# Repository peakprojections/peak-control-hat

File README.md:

# peak-control-hat
KiCad schematic and build files for the Peak Control Hat used with the Peak Controller Raspberry Pi

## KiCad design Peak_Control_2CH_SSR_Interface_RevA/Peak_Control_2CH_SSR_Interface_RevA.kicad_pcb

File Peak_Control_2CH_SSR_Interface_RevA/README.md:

# Peak Control 2CH SSR Interface Rev A1.1

This directory is the first-revision **simple/production-oriented 2-Channel SSR version** of the Peak Projections Power Control Interface Board.

It is intentionally separate from `Peak_Control_HAT_RevA`, which remains the more advanced smart-switch/TPS272C45 design for possible future development. 

It is a scaled down version of the `Peak_Control_SSR_Interface_RevA` which is the 4-channel version.

## Design goals

- Keep the first hardware revision simple, robust, and economical.
- Use Omron PhotoMOS SSRs for isolated 24 V contactor/control outputs.
- Keep mains/load switching off-board; this board controls 24 V contactor coils from low-voltage control circuits only.

## Proposed board

- Raspberry Pi M2.5 mounting pattern
- 24 V control input
- 2 isolated 24 V switched outputs

## Output architecture

Primary SSR: **Omron G3VM-61GR2** (60 V PhotoMOS, SOP-4).

Each output channel is conceptually:

`Pi GPIO -> 390R -> G3VM-61GR2 input LED`

`+24V field -> G3VM-61GR2 output -> SW +24V terminal -> external contactor coil -> field 0V`

Each channel also includes board-side flyback suppression across the output terminals.

## Practical Implementations

This board is designed to work with a Raspberry Pi and has a mounting-hole pattern to be stacked above or below a Pi (long standoffs should be used to keep a distance). 

This board should support any 3.3v output microcontroller connection, it does not have to be a Raspberry Pi.

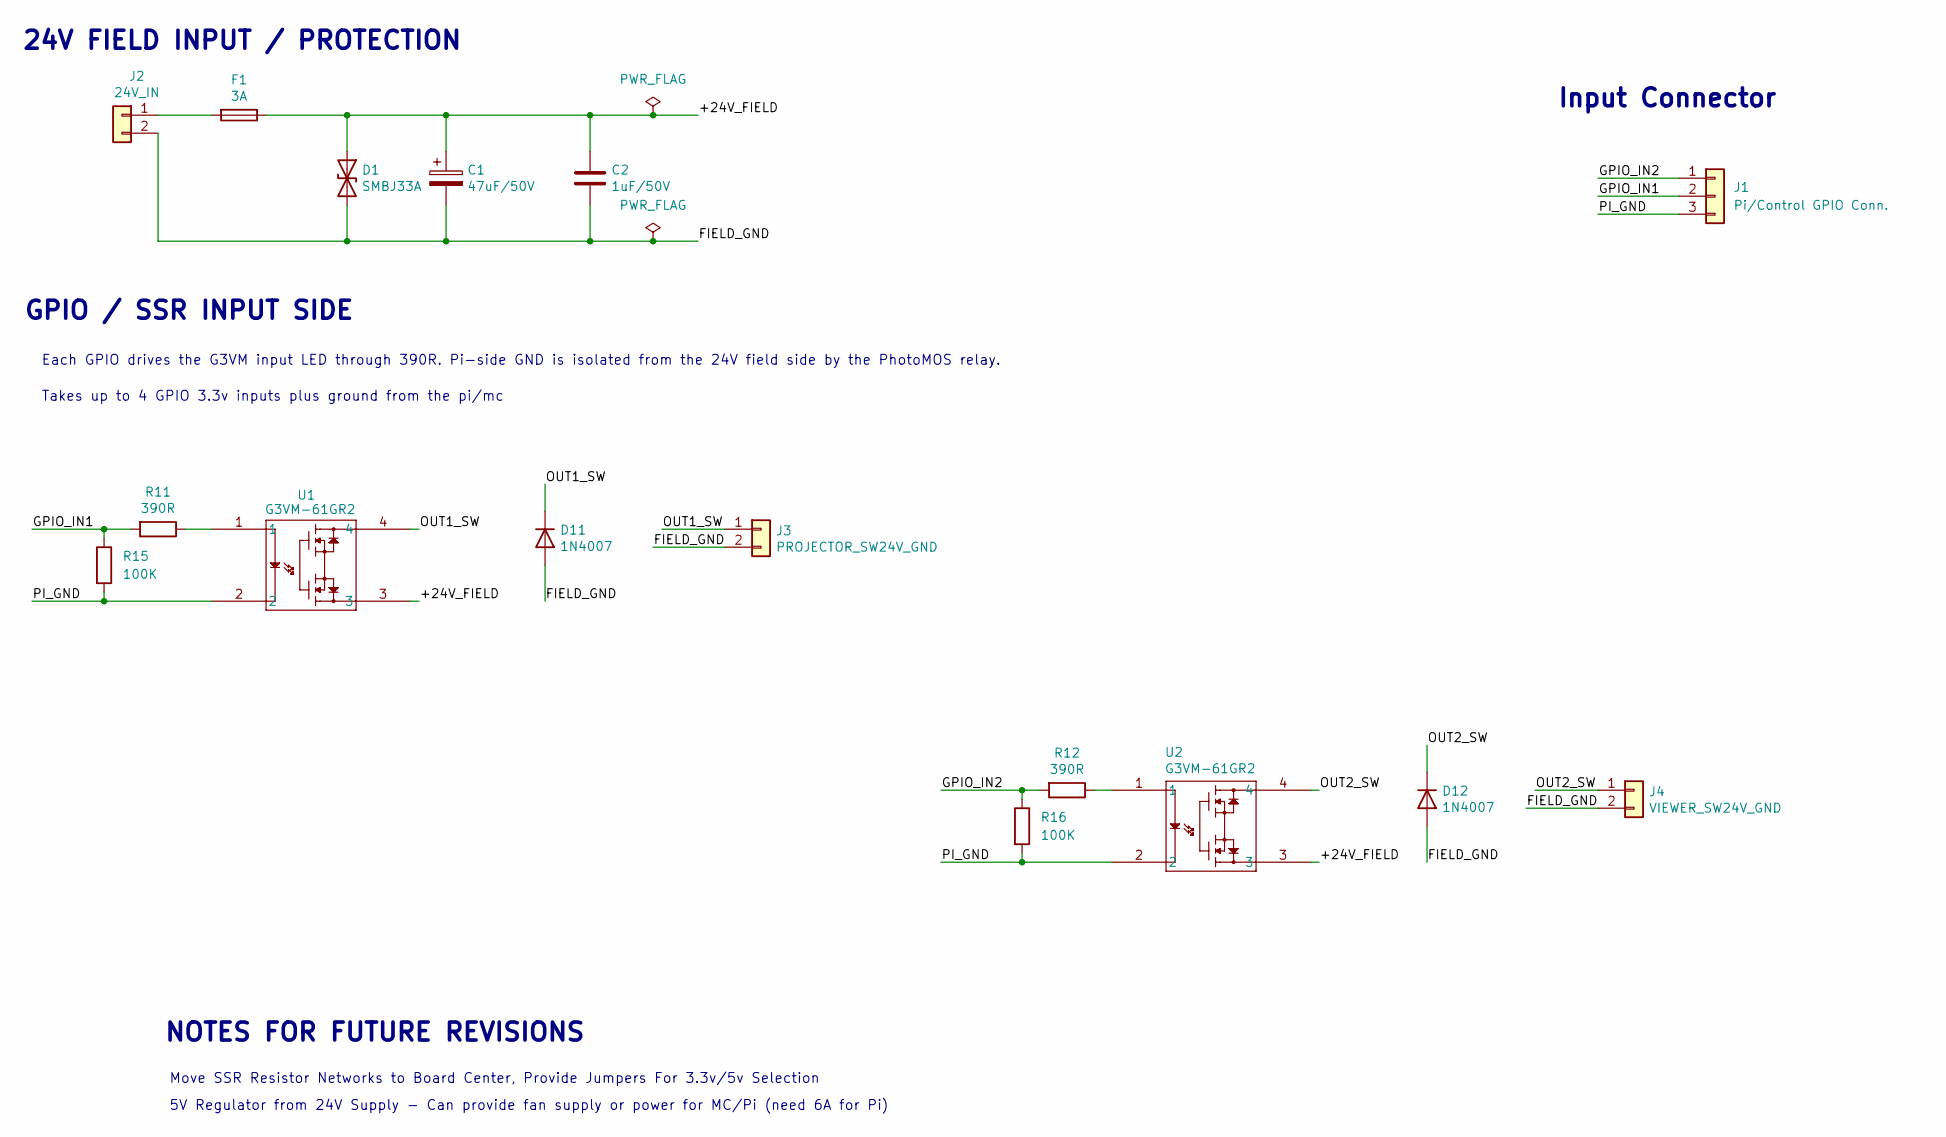
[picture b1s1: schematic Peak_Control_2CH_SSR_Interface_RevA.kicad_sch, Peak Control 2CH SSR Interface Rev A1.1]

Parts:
C1: 47uF/50V; CP_Radial_D8.0mm_P3.50mm; MPN 50RX3047MT78X11.5
C2: 1uF/50V; C_0805_2012Metric_Pad1.18x1.45mm_HandSolder; MPN 08055C105K4T2A
D1: SMBJ33A; D_SMB_Handsoldering; MPN SMBJ33A
D11, D12: 1N4007; D_DO-41_SOD81_P10.16mm_Horizontal; MPN 1N4007
F1: 3A; FUSE-TH_L22.6-W9.0; MPN 5x20 BLX-A XC-7
J1: Pi/Control GPIO Conn.; CONN-TH_3P-P5.08_DIBO_DB128V-5.08-3P-X; MPN DB128V-5.08-3P-GN-S
J2: 24V_IN; CONN-TH_YC0220500000G; MPN YC0220500000G
J3: PROJECTOR_SW24V_GND; CONN-TH_YC0220500000G; MPN YC0220500000G
J4: VIEWER_SW24V_GND; CONN-TH_YC0220500000G; MPN YC0220500000G
R11, R12: 390R; R_0805_2012Metric_Pad1.20x1.40mm_HandSolder; MPN RC0805FR-07390RL
R15, R16: 100K; R_0805_2012Metric_Pad1.20x1.40mm_HandSolder; MPN RC0805FR-07100KL
U1, U2: G3VM-61GR2; G-SOP4_OMR; MPN G3VM-61GR2(TR05)

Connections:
/+24V_FIELD: C1.1, C2.1, D1.1 (A1), F1.1, U1.3, U2.3
/FIELD_GND: C1.2, C2.2, D1.2 (A2), D11.2 (A), D12.2 (A), J2.2, J3.2, J4.2
/GPIO_IN1: J1.2, R11.2, R15.1
/GPIO_IN2: J1.1, R12.2, R16.1
/OUT1_SW: D11.1 (K), J3.1, U1.4
/OUT2_SW: D12.1 (K), J4.1, U2.4
/PI_GND: J1.3, R15.2, R16.2, U1.2, U2.2
unnamed: F1.2, J2.1
unnamed: R11.1, U1.1
unnamed: R12.1, U2.1

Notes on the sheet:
NOTES FOR FUTURE REVISIONS
Each GPIO drives the G3VM input LED through 390R. Pi-side GND is isolated from the 24V field side by the PhotoMOS relay.
5V Regulator from 24V Supply - Can provide fan supply or power for MC/Pi (need 6A for Pi)
Input Connector
24V FIELD INPUT / PROTECTION
GPIO / SSR INPUT SIDE
Move SSR Resistor Networks to Board Center, Provide Jumpers For 3.3v/5v Selection
Takes up to 4 GPIO 3.3v inputs plus ground from the pi/mc

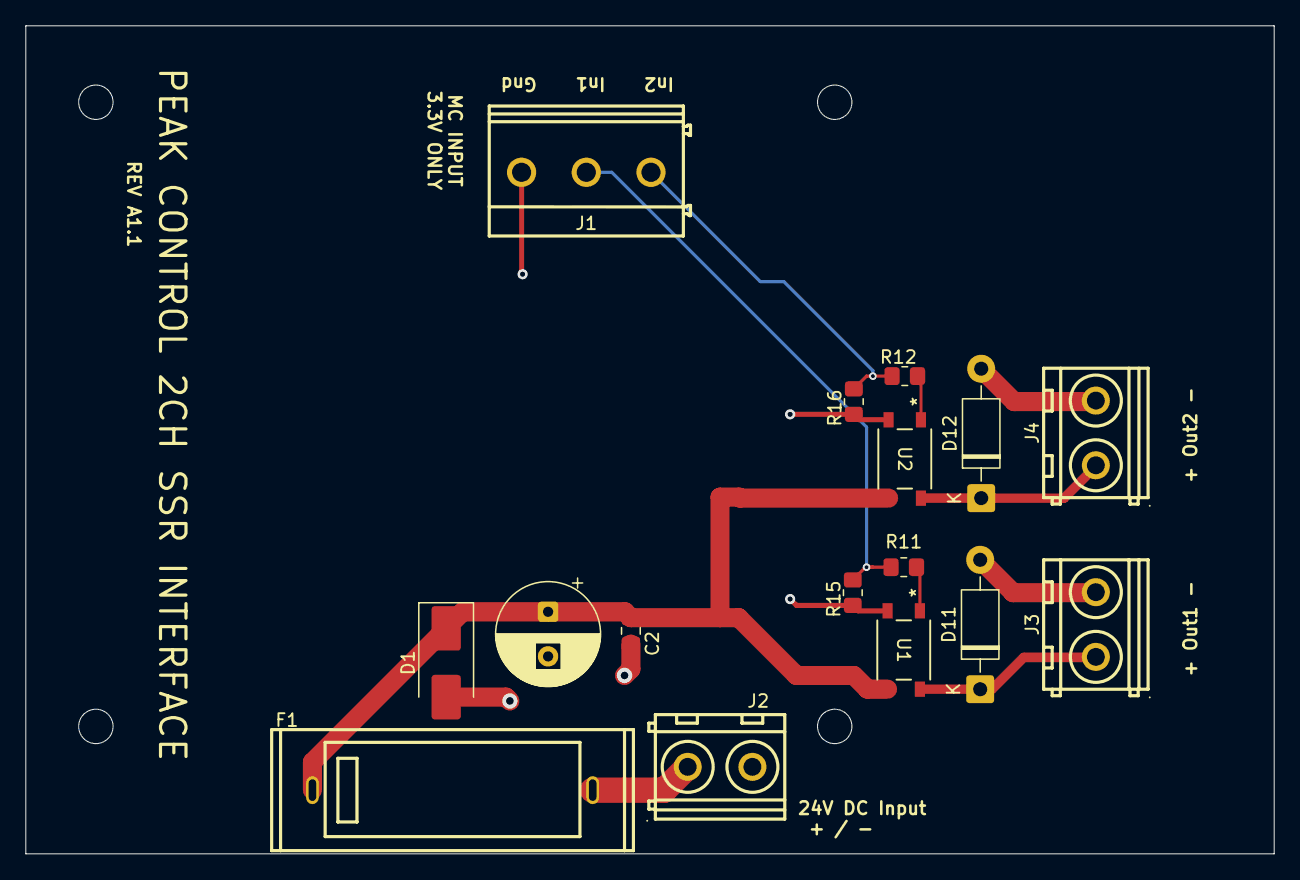
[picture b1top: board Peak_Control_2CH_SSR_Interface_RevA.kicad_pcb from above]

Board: 4 copper layers, 98.0 x 65.0 mm, 16 parts (0 on the bottom side), 10 nets.

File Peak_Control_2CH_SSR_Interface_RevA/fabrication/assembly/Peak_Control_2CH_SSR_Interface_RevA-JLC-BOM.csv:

Comment,Designator,Footprint,LCSC Part #
47uF/50V,C1,CP_Radial_D8.0mm_P3.50mm,C473223
1uF/50V,C2,C_0805_2012Metric_Pad1.18x1.45mm_HandSolder,C779994
SMBJ33A,D1,D_SMB_Handsoldering,C5261717
1N4007,"D11,D12",D_DO-41_SOD81_P10.16mm_Horizontal,C106903
3A,F1,FUSE-TH_L22.6-W9.0,C3131
Pi/Control GPIO Conn.,J1,CONN-TH_3P-P5.08_DIBO_DB128V-5.08-3P-X,C2915640
24V_IN,J2,CONN-TH_YC0220500000G,C2683165
PROJECTOR_SW24V_GND,J3,CONN-TH_YC0220500000G,C2683165
VIEWER_SW24V_GND,J4,CONN-TH_YC0220500000G,C2683165
390R,"R11,R12",R_0805_2012Metric_Pad1.20x1.40mm_HandSolder,C114543
100K,"R15,R16",R_0805_2012Metric_Pad1.20x1.40mm_HandSolder,C96346
G3VM-61GR2,"U1,U2",G-SOP4_OMR,C2653911

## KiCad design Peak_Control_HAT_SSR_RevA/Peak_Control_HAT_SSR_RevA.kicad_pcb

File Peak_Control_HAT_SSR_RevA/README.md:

# Peak Control HAT SSR Rev A

This directory is the first-revision **simple/production-oriented SSR version** of the Peak Projections Power Control HAT.

It is intentionally separate from `Peak_Control_HAT_RevA`, which remains the more advanced smart-switch/TPS272C45 design for possible future development.

## Design goals

- Keep the first hardware revision simple, robust, and economical.
- Use Omron PhotoMOS SSRs for isolated 24 V contactor/control outputs.
- Preserve the Raspberry Pi GPIO mapping used by the advanced design where practical so software can remain hardware-agnostic.
- Retain the corrected Raspberry Pi HAT mechanical geometry from the existing design.
- Provide I2C expansion directly from the Pi for future diagnostics/display/daughterboards.
- Keep mains/load switching off-board; this HAT controls 24 V contactor coils and low-voltage control circuits only.

## Proposed board

- 115 mm × 70 mm extended HAT-style PCB target
- Raspberry Pi 2×20 stacking header
- Raspberry Pi M2.5 mounting pattern
- 40 mm fan mechanical provision retained
- 24 V control input
- 4 isolated 24 V switched outputs
- 2 field/proof inputs
- 2 IR output connections
- 4-position I2C expansion terminal: `3V3`, `GND`, `SDA`, `SCL`
- 3-wire fan connector: `5V`, `GND`, `TACH`

## Output architecture

Primary SSR: **Omron G3VM-61GR2** (60 V PhotoMOS, SOP-4).

Each output channel is conceptually:

`Pi GPIO -> 390R -> G3VM-61GR2 input LED`

`+24V field -> G3VM-61GR2 output -> SW +24V terminal -> external contactor coil -> field 0V`

Each channel also includes board-side flyback suppression across the output terminals.

## I2C expansion

A dedicated 4-position terminal block is included:

1. 3V3
2. GND
3. SDA (GPIO2 / physical pin 3)
4. SCL (GPIO3 / physical pin 5)

Optional SDA/SCL pull-up footprints are intended to be DNP by default because the Raspberry Pi already supplies I2C pull-ups. Series-resistor footprints allow 0-ohm links initially or modest damping if useful during testing.

Raw I2C should be treated as a short-range internal expansion interface. Longer remote runs should eventually use an appropriate extender, CAN, RS-485, or similar robust field bus.

## Current files

- `Peak_Control_HAT_SSR_RevA.sch` — initial schematic source in KiCad legacy format, ready to open/import and save into the current `.kicad_sch` format.
- `Peak_Control_HAT_SSR_RevA.kicad_pcb` — separate SSR mechanical/placement skeleton using the corrected Pi/header/mounting geometry.
- `Peak_Control_HAT_SSR_RevA.kicad_pro` — project container; KiCad will populate normal project settings when opened/saved.
- `Electrical_Design_SSR_RevA.md` — electrical architecture, protection intent, routing targets, and fabrication hold points.
- `Pin_Map_SSR_RevA.csv` — GPIO/function map for the simplified board.

## Important fabrication note

The G3VM symbols and PCB locations are currently **design placeholders**. The exact Omron G3VM-61GR2 pin numbering and recommended SOP-4 land pattern must be verified and substituted before routing or fabrication. The proof-input, IR-buffer, and fan-control circuits also remain to be finalized.

## Status

The SSR revision is now established as an independent project without modifying the TPS-based design. The next step is to open/import the schematic in KiCad, save it in the current `.kicad_sch` format, then continue detailed schematic capture and verified footprint assignment before routing.

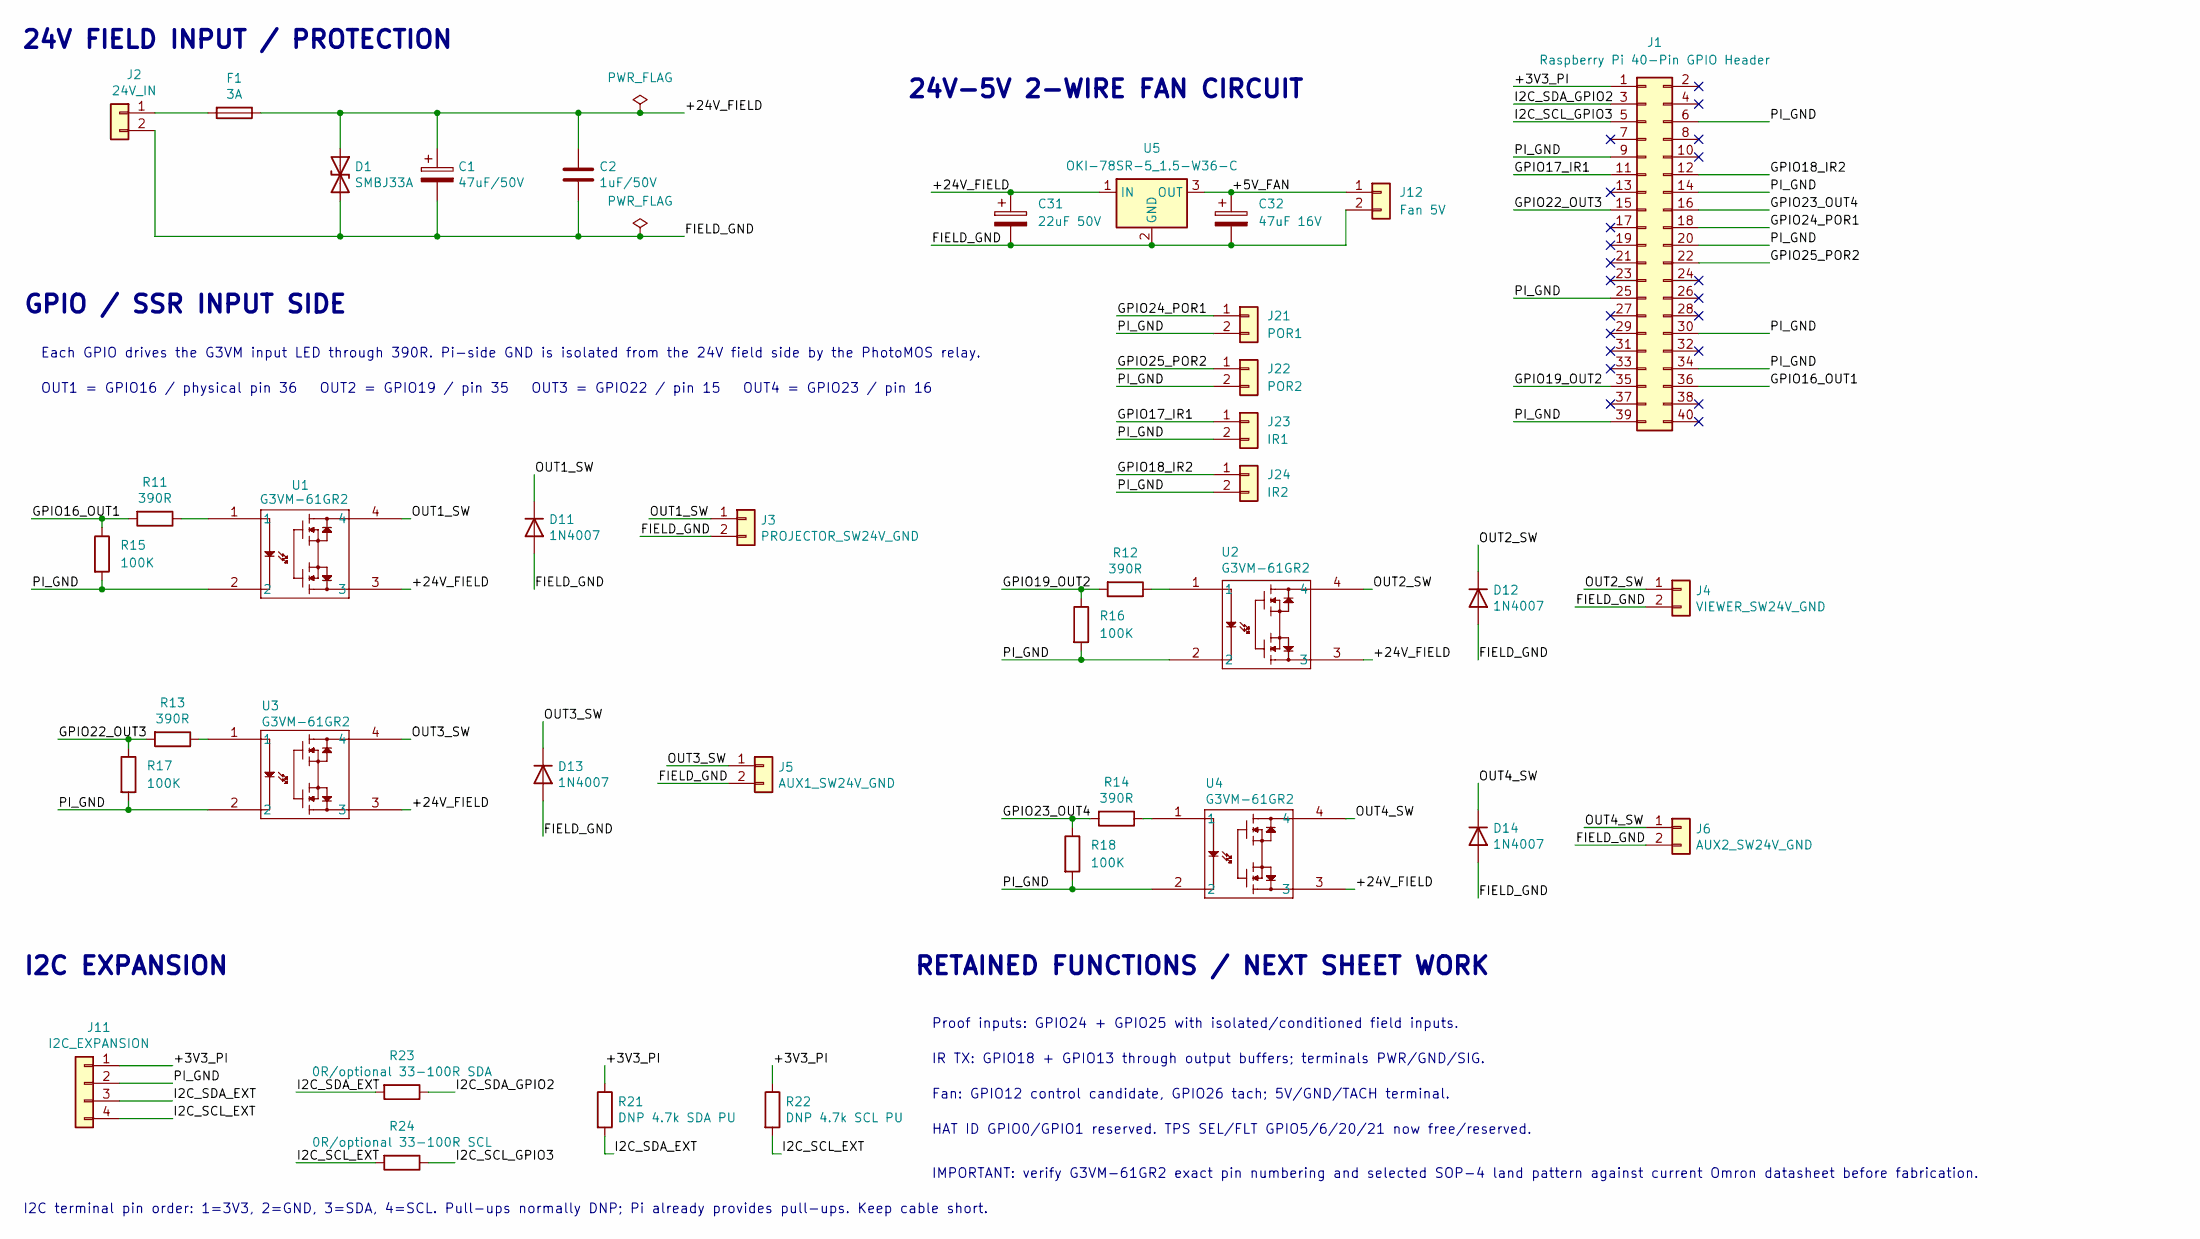
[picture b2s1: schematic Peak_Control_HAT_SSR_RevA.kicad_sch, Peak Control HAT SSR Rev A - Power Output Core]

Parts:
C1: 47uF/50V; CP_Radial_D8.0mm_P3.50mm
C2: 1uF/50V; C_0805_2012Metric_Pad1.18x1.45mm_HandSolder
C31: 22uF 50V; CP_Radial_D5.0mm_P2.00mm
C32: 47uF 16V; CP_Radial_D5.0mm_P2.00mm
D1: SMBJ33A; D_SMB_Handsoldering
D11, D12, D13, D14: 1N4007; D_DO-41_SOD81_P10.16mm_Horizontal
F1: 3A; Fuseholder_Clip-5x20mm_Bel_FC-203-22_Lateral_P17.80x5.00mm_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
J1: Raspberry Pi 40-Pin GPIO Header; PinSocket_2x20_P2.54mm_Vertical
J2: 24V_IN; TerminalBlock_Phoenix_MKDS-1,5-2-5.08_1x02_P5.08mm_Horizont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
J3: PROJECTOR_SW24V_GND; TerminalBlock_Phoenix_MKDS-1,5-2-5.08_1x02_P5.08mm_Horizont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
J4: VIEWER_SW24V_GND; TerminalBlock_Phoenix_MKDS-1,5-2-5.08_1x02_P5.08mm_Horizont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
J5: AUX1_SW24V_GND; TerminalBlock_Phoenix_MKDS-1,5-2-5.08_1x02_P5.08mm_Horizont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
J6: AUX2_SW24V_GND; TerminalBlock_Phoenix_MKDS-1,5-2-5.08_1x02_P5.08mm_Horizont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
J11: I2C_EXPANSION; TerminalBlock_Phoenix_MKDS-1,5-4-5.08_1x04_P5.08mm_Horizont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
J12: Fan 5V; JST_XH_B2B-XH-A_1x02_P2.50mm_Vertical
J21: POR1; TerminalBlock_Phoenix_MKDS-1,5-2-5.08_1x02_P5.08mm_Horizont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
J22: POR2; TerminalBlock_Phoenix_MKDS-1,5-2-5.08_1x02_P5.08mm_Horizont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
J23: IR1; TerminalBlock_Phoenix_MKDS-1,5-2-5.08_1x02_P5.08mm_Horizont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
J24: IR2; TerminalBlock_Phoenix_MKDS-1,5-2-5.08_1x02_P5.08mm_Horizont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
R11, R12, R13, R14: 390R; R_0805_2012Metric_Pad1.20x1.40mm_HandSolder
R15, R16, R17, R18: 100K; R_0805_2012Metric_Pad1.20x1.40mm_HandSolder
R21: DNP 4.7k SDA PU; R_0805_2012Metric_Pad1.20x1.40mm_HandSolder
R22: DNP 4.7k SCL PU; R_0805_2012Metric_Pad1.20x1.40mm_HandSolder
R23: 0R/optional 33-100R SDA; R_0805_2012Metric_Pad1.20x1.40mm_HandSolder
R24: 0R/optional 33-100R SCL; R_0805_2012Metric_Pad1.20x1.40mm_HandSolder
U1, U2, U3, U4: G3VM-61GR2; G-SOP4_OMR
U5: OKI-78SR-5_1.5-W36-C; Converter_DCDC_Murata_OKI-78SR_Vertical

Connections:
/+3V3_PI: J1.1, J11.1, R21.1, R22.1
/+5V_FAN: C32.1, J12.1, U5.3 (OUT)
/+24V_FIELD: C1.1, C2.1, C31.1, D1.1 (A1), F1.1, U1.3, U2.3, U3.3, U4.3, U5.1 (IN)
/FIELD_GND: C1.2, C2.2, C31.2, C32.2, D1.2 (A2), D11.2 (A), D12.2 (A), D13.2 (A), D14.2 (A), J2.2, J3.2, J4.2, J5.2, J6.2, J12.2, U5.2 (GND)
/GPIO16_OUT1: J1.36, R11.2, R15.1
/GPIO17_IR1: J1.11, J23.1
/GPIO18_IR2: J1.12, J24.1
/GPIO19_OUT2: J1.35, R12.2, R16.1
/GPIO22_OUT3: J1.15, R13.2, R17.1
/GPIO23_OUT4: J1.16, R14.2, R18.1
/GPIO24_POR1: J1.18, J21.1
/GPIO25_POR2: J1.22, J22.1
/I2C_SCL_EXT: J11.4, R22.2, R24.2
/I2C_SCL_GPIO3: J1.5, R24.1
/I2C_SDA_EXT: J11.3, R21.2, R23.2
/I2C_SDA_GPIO2: J1.3, R23.1
/OUT1_SW: D11.1 (K), J3.1, U1.4
/OUT2_SW: D12.1 (K), J4.1, U2.4
/OUT3_SW: D13.1 (K), J5.1, U3.4
/OUT4_SW: D14.1 (K), J6.1, U4.4
/PI_GND: J1.6, J1.9, J1.14, J1.20, J1.25, J1.30, J1.34, J1.39, J11.2, J21.2, J22.2, J23.2, J24.2, R15.2, R16.2, R17.2, R18.2, U1.2, U2.2, U3.2, U4.2
unnamed: F1.2, J2.1
unnamed: R11.1, U1.1
unnamed: R12.1, U2.1
unnamed: R13.1, U3.1
unnamed: R14.1, U4.1

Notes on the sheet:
I2C EXPANSION
HAT ID GPIO0/GPIO1 reserved. TPS SEL/FLT GPIO5/6/20/21 now free/reserved.
RETAINED FUNCTIONS / NEXT SHEET WORK
Each GPIO drives the G3VM input LED through 390R. Pi-side GND is isolated from the 24V field side by the PhotoMOS relay.
24V-5V 2-WIRE FAN CIRCUIT
IMPORTANT: verify G3VM-61GR2 exact pin numbering and selected SOP-4 land pattern against current Omron datasheet before fabrication.
24V FIELD INPUT / PROTECTION
GPIO / SSR INPUT SIDE
I2C terminal pin order: 1=3V3, 2=GND, 3=SDA, 4=SCL. Pull-ups normally DNP; Pi already provides pull-ups. Keep cable short.
Proof inputs: GPIO24 + GPIO25 with isolated/conditioned field inputs.
Fan: GPIO12 control candidate, GPIO26 tach; 5V/GND/TACH terminal.
IR TX: GPIO18 + GPIO13 through output buffers; terminals PWR/GND/SIG.
OUT1 = GPIO16 / physical pin 36 OUT2 = GPIO19 / pin 35 OUT3 = GPIO22 / pin 15 OUT4 = GPIO23 / pin 16

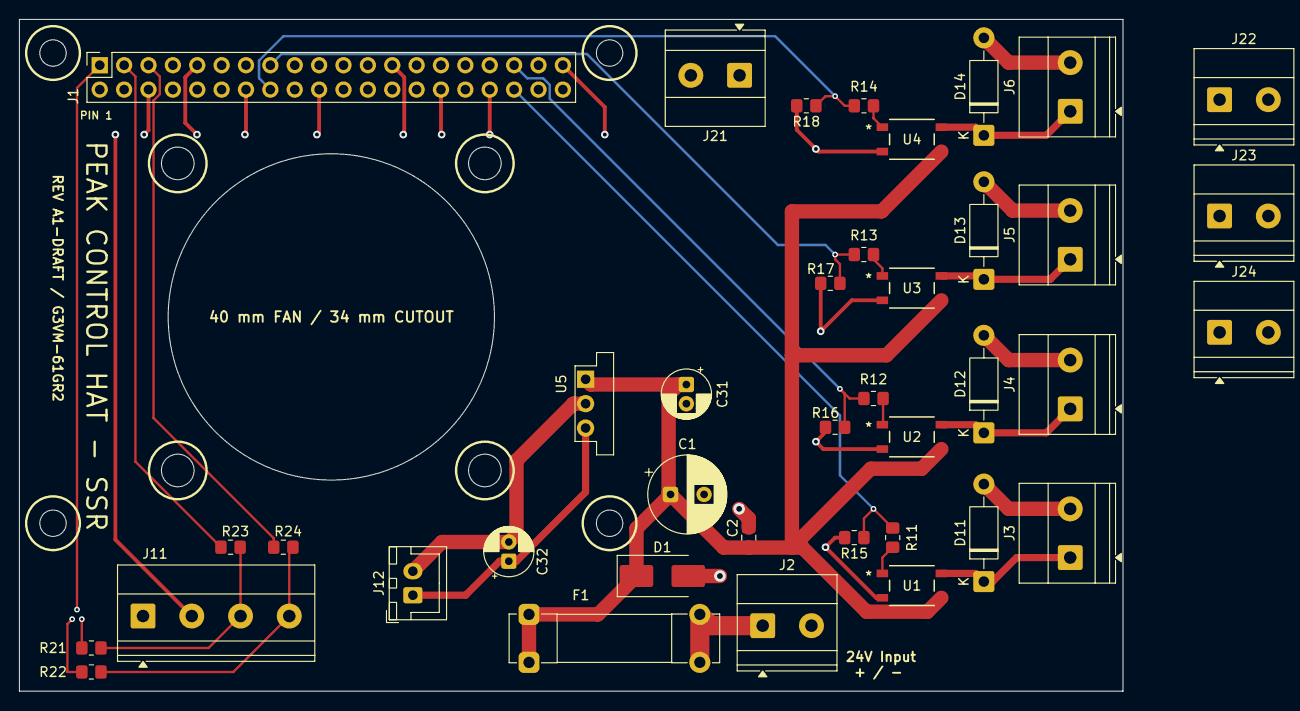
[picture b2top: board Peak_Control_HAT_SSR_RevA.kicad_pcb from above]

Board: 4 copper layers, 115.0 x 70.0 mm, 39 parts (0 on the bottom side), 26 nets.
